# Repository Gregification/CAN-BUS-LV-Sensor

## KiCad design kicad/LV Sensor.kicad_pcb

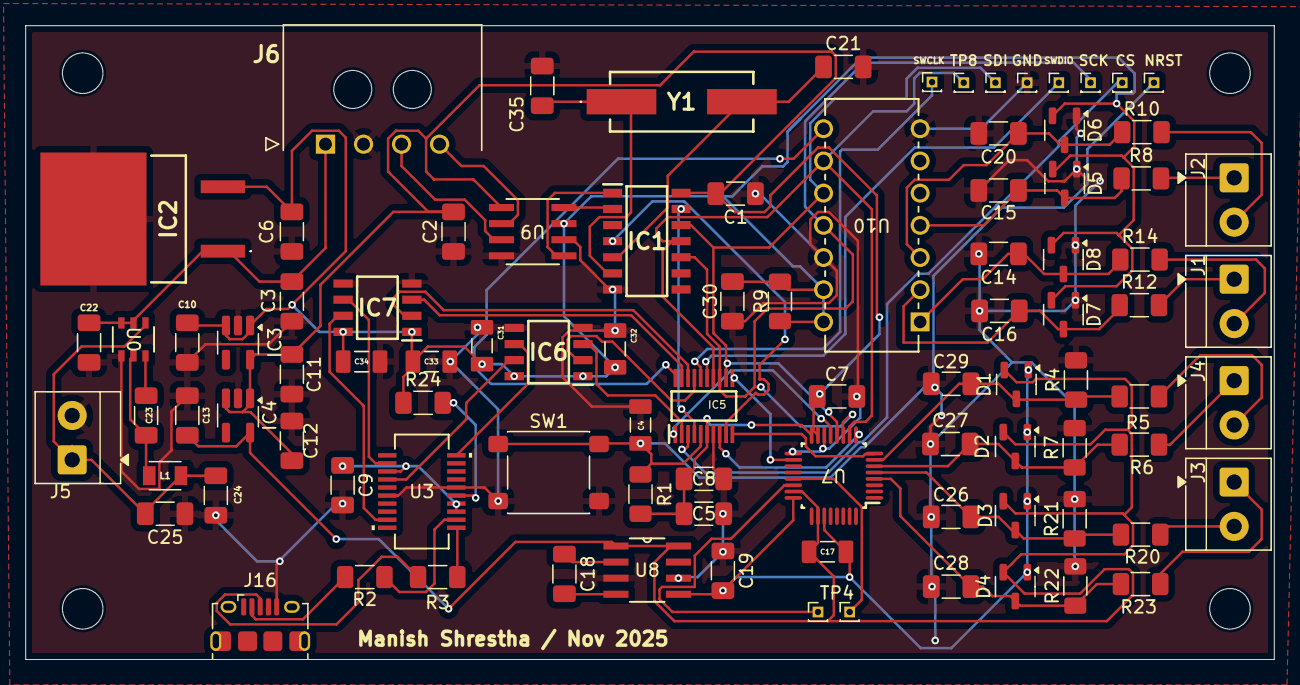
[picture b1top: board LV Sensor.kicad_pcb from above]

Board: 2 copper layers, 98.5 x 50.0 mm, 97 parts (0 on the bottom side), 63 nets.

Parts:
C1, C2, C7, C8, C9, C14, C15, C16, C20, C23, C26, C27, C28, C29, C30: 0.1uF; C_1206_3216Metric_Pad1.33x1.80mm_HandSolder
C3, C5, C6, C22: 10uF; C_1206_3216Metric_Pad1.33x1.80mm_HandSolder
C4: 0.01 uF; CAPC3216X140N
C10, C11, C12, C13: 1uF; C_1206_3216Metric_Pad1.33x1.80mm_HandSolder
C17: 330nF; CAPC3216X100N
C18, C19: 47µF; C_1206_3216Metric_Pad1.33x1.80mm_HandSolder
C21, C35: 47pF; C_1206_3216Metric_Pad1.33x1.80mm_HandSolder
C24, C25: 22uF; C_1206_3216Metric_Pad1.33x1.80mm_HandSolder
C31, C32, C33, C34: 0.01uF; CAPC3216X140N
D1, D2, D3, D4, D5, D6, D7, D8: BAT54S; SOT-23-3
H1, H2, H3, H4: MountingHole; MountingHole_3.2mm_M3
IC1: MCP2517FDT-H_SL; CAN_FD_SOIC127P600X175-14N
IC2: MC7805CD2TR4G
IC3: TLV74133PDBVR; SOT-23-5_HandSoldering
IC4: TLV74125PDBVR; SOT-23-5_HandSoldering
IC5: MSPM0C1104SDGS20R; SOP50P490X110-20N
IC6, IC7: ISO6721BDR; SOIC127P600X175-8N
J1, J2, J3, J4, J5: Screw_Terminal_01x02; TerminalBlock_MetzConnect_Type059_RT06302HBWC_1x02_P3.50mm_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
J6: 43650-0401; 43650-04_00,01,02_
J16: USB_B_Micro; USB_Micro-B_Amphenol_10118194-0001LF_Horizontal
L1: 4.7uH; L_TDK_NLV25_2.5x2.0mm
R1: 47.5k; R_1206_3216Metric_Pad1.30x1.75mm_HandSolder
R2, R3: 27R; R_1206_3216Metric_Pad1.30x1.75mm_HandSolder
R4, R7, R21, R22, R24: 10k; R_1206_3216Metric_Pad1.30x1.75mm_HandSolder
R5, R6, R20, R23: ~62k; R_1206_3216Metric_Pad1.30x1.75mm_HandSolder
R8, R9, R10, R12, R14: 20k; R_1206_3216Metric_Pad1.30x1.75mm_HandSolder
SW1: SW_Push; SW_SPST_PTS645Sx43SMTR92
TP1, TP2, TP3, TP4, TP5, TP6, TP7, TP8, TP9, TP10: TestPoint; PinHeader_1x01_P1.00mm_Vertical
U0: AP63205WU-7; AP6320xWU-7_DIO
U3: FT231XS-R; SSOP-20_FTD
U7: ADS114S06BIPBSR; PBS0032A_N
U8: LM2662MX/NOPB; M08A
U9: ATA6561-GAQW-N; SOIC8_4P9X3P9MC_MCH
U10: MCP3204-CI/P; PDIP14_300MC_MCH
Y1: 830017146

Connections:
+2V5: C13.1, C17.2, D1.2 (K), D2.2 (K), D3.2 (K), D4.2 (K), IC4.5 (OUT), U7.23 (REFOUT), U7.26 (AVDD), U8.1 (FC), U8.8 (V+)
+3V3: C1.2, C2.2, C5.1, C7.2, C8.1, C11.1, C12.1, IC1.14 (VDD), IC3.5 (OUT), IC4.1 (IN), IC4.3 (EN), IC5.6 (VDD), R1.2, U7.15 (IOVDD), U7.16 (DVDD), U9.5 (VIO)
+5V: C6.1, C10.2, C30.1, C31.2, C32.2, C33.2, C34.2, D5.2 (K), D6.2 (K), D7.2 (K), D8.2 (K), IC2.3 (OUTPUT), IC3.1 (IN), IC3.3 (EN), IC6.1 (VCC1), IC6.8 (VCC2), IC7.1 (VCC1), IC7.8 (VCC2), R9.1, R9.2, R24.1, U9.3 (VCC), U10.13 (VREF), U10.14 (VDD)
+12V: C3.2, C22.1, IC2.1 (INPUT), J6.1, U0.2 (EN), U0.3 (VIN)
-2V5: C17.1, C19.2, D1.1 (A), D2.1 (A), D3.1 (A), D4.1 (A), U7.24 (REFCOM), U7.27 (AVSS), U8.5 (OUT)
/5V out: C24.2, C25.2, J5.1, L1.1, U0.1 (FB)
ADC_DRDY: IC5.1 (PA26_/_A1), U7.13 (DRDY_N)
ADC_RESET: IC5.11 (PA11), U7.18 (RESET_N)
ADC_START: IC5.10 (PA6), U7.8 (START_SYNC)
CAN_FD_INT: IC1.4 (~INT), IC5.9 (PA4)
CAN_H: J6.3, U9.7 (CANH)
CAN_L: J6.4, U9.6 (CANL)
CS_ADC4: IC5.20 (PA25_/_A2), U10.8 (CS/SHDN)
CS_ADC8: IC5.8 (PA2), U7.9 (CS_N)
CS_CAN: IC1.13 (NCS), IC5.4 (PA0)
EXTERNAL_CS: IC5.3 (PA28_/_A5), TP7.1
GND: C1.1, C2.1, C3.1, C4.1, C5.2, C6.2, C7.1, C8.2, C9.2, C10.1, C11.2, C12.2, C13.2, C14.2, C15.1, C16.2, C19.1, C20.2, C21.2, C22.2, C24.1, C25.1, C26.2, C27.1, C28.1, C29.2, C30.2, C31.1, C32.1, C33.1, C34.1, C35.2, D5.1 (A), D6.1 (A), D7.1 (A), D8.1 (A), IC1.7 (VSS), IC2.2 (GROUND), IC3.2 (GND), IC4.2 (GND), IC5.7 (VSS), IC6.4 (GND1), IC6.5 (GND2), IC7.4 (GND1), IC7.5 (GND2), J5.2, J6.2, J16.5 (GND), R4.2, R7.2, R21.2, R22.2, SW1.2, TP5.1, U0.4 (GND), U3.6 (GND), U3.16 (GND), U7.14 (DGND), U7.17 (CLK), U8.3 (GND), U8.6 (LV), U9.2 (GND), U9.8 (STBY), U10.7 (DGND), U10.12 (AGND)
NRST: C4.2, IC5.5 (PA1_/_NRST), R1.1, SW1.1, TP6.1
unnamed: C29.1, D1.3 (COM), R4.1, R5.1, U7.7 (AIN0)
unnamed: C27.2, D2.3 (COM), R6.2, R7.1, U7.6 (AIN1)
unnamed: C26.1, D3.3 (COM), R20.1, R21.1, U7.5 (AIN2)
unnamed: C28.2, D4.3 (COM), R22.1, R23.2, U7.4 (AIN3)
unnamed: C15.2, D5.3 (COM), R8.1, U10.4 (CH3)
unnamed: C20.1, D6.3 (COM), R10.1, U10.3 (CH2)
unnamed: C16.1, D7.3 (COM), R12.1, U10.2 (CH1)
unnamed: C14.1, D8.3 (COM), R14.1, U10.1 (CH0)
unnamed: C35.1, IC1.6 (OSC1), Y1.1
unnamed: C21.1, IC1.5 (OSC2), Y1.2
unnamed: IC1.2 (RXCAN), U9.4 (RXD)
unnamed: IC1.1 (TXCAN), U9.1 (TXD)
unnamed: IC5.15 (PA19_/_SWDIO), TP2.1
unnamed: IC5.16 (PA20_/_A6_/_SWCLK), TP1.1
unnamed: J1.1, R12.2
unnamed: J1.2, R14.2
unnamed: J2.1, R8.2
unnamed: J2.2, R10.2
unnamed: J3.1, R23.1
unnamed: J3.2, R20.2
unnamed: J4.1, R6.1
unnamed: J4.2, R5.2
unnamed: J16.3 (D+), R3.1
unnamed: J16.2 (D-), R2.1
unnamed: C23.1, U0.6 (BST)
unnamed: C23.2, L1.2, U0.5 (SW)
unnamed: C9.1, U3.3 (VCCIO), U3.13 (3V3OUT), U3.14 (RESET#)
unnamed: R2.2, U3.12 (USBDM)
unnamed: R3.2, U3.11 (USBDP)
unnamed: R24.2, U3.15 (VCC)
unnamed: TP3.1, U7.22 (GPIO0)
unnamed: TP4.1, U7.21 (GPIO1)
unnamed: C18.1, U8.2 (C1+)
unnamed: C18.2, U8.4 (C1-)
SCK: IC1.10 (SCK), IC5.13 (PA17), TP10.1, U7.11 (SCLK), U10.11 (CLK)
SDI: IC1.12 (SDO), IC5.12 (PA16_/_A8), TP9.1, U7.12 (DOUT_DRDY_N), U10.10 (DOUT)
SDO: IC1.11 (SDI), IC5.14 (PA18_/_A7), TP8.1, U7.10 (DIN), U10.9 (DIN)
UART0_CTS: IC5.18 (PA23), IC7.2 (OUTA)
UART0_CTS_ISOLA: IC7.7 (INA), U3.9 (CTS#)
UART0_RTS: IC5.19 (PA24_/_A3), IC7.3 (INB)
UART0_RTS_ISOLA: IC7.6 (OUTB), U3.2 (RTS#)
UART0_RX: IC5.17 (PA22_/_A4), IC6.2 (OUTA)
UART0_RX_ISOLA: IC6.7 (INA), U3.4 (RXD)
UART0_TX: IC5.2 (PA27_/_A0), IC6.3 (INB)
UART0_TX_ISOLA: IC6.6 (OUTB), U3.20 (TXD)

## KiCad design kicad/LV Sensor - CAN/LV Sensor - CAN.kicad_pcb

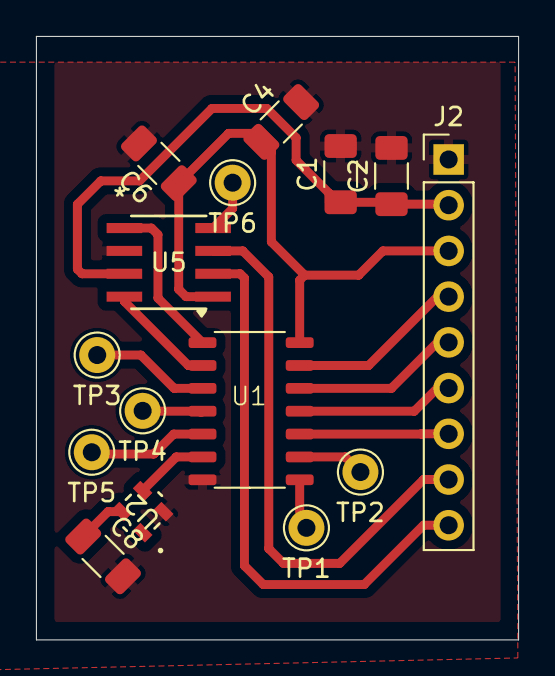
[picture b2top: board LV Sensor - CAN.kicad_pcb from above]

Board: 2 copper layers, 26.8 x 33.5 mm, 15 parts (0 on the bottom side), 18 nets.

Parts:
C1, C2, C4, C6: 100nF; C_1206_3216Metric_Pad1.33x1.80mm_HandSolder
C8: 15pF; C_1206_3216Metric_Pad1.33x1.80mm_HandSolder
J2: Conn_01x09_Pin; PinHeader_1x09_P2.54mm_Vertical
TP1, TP2, TP3, TP4, TP5, TP6: TestPoint; Pin_D1.0mm_L10.0mm
U1: MCP2518FD-xJHA; MCP2518FDT
U2: DSC1001DL5-020.0000T; CDFN4_2P5X2_MCH
U5: ATA6561-GAQW-N; SOIC8_4P9X3P9MC_MCH

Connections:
+3.3V: C4.1, C6.1, C8.1, J2.3, U1.14 (VDD), U2.4 (VDD), U5.5 (VIO)
+5V: C1.1, C2.1, J2.2, U5.3 (VCC)
/CAN_H: J2.8, U5.7 (CANH)
/CAN_L: J2.9, U5.6 (CANL)
GND: C1.2, C2.2, C4.2, C6.2, C8.2, J2.1, U1.7 (VSS), U2.2 (GND), U5.2 (GND)
unnamed: J2.4, U1.13 (~CS)
unnamed: J2.5, U1.12 (SDO)
unnamed: J2.6, U1.11 (SDI)
unnamed: J2.7, U1.10 (SCK)
unnamed: TP3.1, U1.3 (CLKO/SOF)
unnamed: U1.6 (OSC1), U2.3 (OUT)
unnamed: TP5.1, U1.5 (OSC2)
unnamed: U1.2 (RXCAN), U5.4 (RXD)
unnamed: U1.1 (TXCAN), U5.1 (TXD)
unnamed: TP2.1, U1.9 (~INT0/GPIO0/XSTBY)
unnamed: TP1.1, U1.8 (~INT1/GPIO1)
unnamed: TP4.1, U1.4 (~INT)
unnamed: TP6.1, U5.8 (STBY)

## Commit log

2025-08-23 08-23-25 Initial Commit
    Yimmpie
2025-08-26 08-25-25 Updated Board
    Everything got deleted because a new copy was saved elsewhere.
2025-08-26 06-26-25 Added OP Amplifier to schematic
2025-08-28 something
2025-08-28 sdfafsdfsfdaf
2025-08-29 08-28-25 Changed symbols to match new components
2025-09-02 gitignored
2025-09-02 Added buck converter to schematic and set it up for use
2025-09-03 Mostly setup CAN, hooked it up to the MCU, and chose the I/O pins to be used on the MCU.
2025-09-03 Completed the voltage inverter; still needs to be hooked up to ADC and a 2.5V reference made for it.
2025-09-04 Pretty much finished everything for now. Just need to condition the analog inputs.
2025-09-05 09-05-2025 Finished Revision.1 of LV Sensor Board
2025-09-05 09-05-2025 Deleted Extra Stuff
2025-09-05 someone pushed the backups
2025-09-05 readded ignore
2025-09-06 09-05-2025 "Finished" LV-Sensor-Can Board
2025-09-06 everything is nasty
2025-09-06 09-06-2025 Final CAN Board
2025-09-06 09-06-2025 Fixed Some Changes
2025-09-06 09-05-2025 Final Again
2025-09-06 09-06-2025 Again
2025-09-09 work faster 🍘
2025-09-11 09-10-25
2025-09-12 SPI files by Marnish Shrestha
2025-09-13 ljklj
    Changed notation 3V3 to 3.3V
2025-09-27 09-26-2005
2025-10-18 I believe I finished the ADC front end.
2025-11-14 trh
    thrsth
2025-11-15 5y5y
    45y45
2025-11-16 aerg
    Completely fixed everything
2025-11-17 rgwg
    fixxes
2025-11-18 fthft
    thhf
2025-11-18 sdfs
    sfds
2025-11-18 gfh
    fghfg
2025-11-19 gtugt
    ugttu
2025-11-19 dfggd
    fd
2025-11-20 fdg
    dgf
2025-11-21 finalized changes
2025-11-21 Final Checks
    Completed Board
2025-11-21 Gerber files added
2025-11-25 finished v1
